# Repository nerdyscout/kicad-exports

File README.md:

**ℹ️ kicad-exports will not be updated anymore! As KiBot itself runs now in CI/CD, and there is this great [template](https://github.com/nerdyscout/KiBot-CICD-Template), even better automation can be done.**

---

Auto generate exports (schematics, gerbers, plots) for any KiCAD5 project.
You could run it locally or on every `git push` with Github Actions.

# usage of kicad-exports with Github Actions
```yaml
name: example

on:
  push:
    paths:
    - '**.sch'
    - '**.kicad_pcb'
  pull_request:
    paths:
      - '**.sch'
      - '**.kicad_pcb'

jobs:
  example:
    runs-on: ubuntu-latest
    steps:
    - uses: actions/checkout@v2
    - uses: nerdyscout/kicad-exports@v2.3.1
      with:
      # Required - kibot config file
        config: any.kibot.yaml
      # optional - prefix to output defined in config
        dir: docs
      # optional - schematic file
        schema: '*.sch'
      # optional - PCB design file
        board: '*.kicad_pcb'
      # optional - verbose output info
        verbose: 0
    - name: upload results
      uses: actions/upload-artifact@v2
      with:
        name: docs
        path: docs
```
The [predefined configs](/config) do run a ERC and DRC in advance, if these checks fail no exports will be generated. You could [write your own config](https://github.com/INTI-CMNB/kibot/tree/v0.8.0#the-configuration-file) file and define [filters](https://github.com/INTI-CMNB/kibot#filtering-drcerc-errors) to ignore these errors therefore forcing to export the data. In this case be careful not to end up with some faulty PCB.

> :warning: Pushing auto generated files back to the same branch you are working on manualy is a bad idea!

# use kicad-exports local 
## Installation
You need to have [Docker](https://www.docker.com/) installed.
```
git clone --recursive https://github.com/nerdyscout/kicad-exports /some/where/kicad-exports
cd /some/where/kicad-exports
make && make install
```

## run
go to your KiCad project folder and run kicad-exports
```
cd /my/kicad/example-project
kicad-exports -d $DIR_OUT -e $SCHEMA -b $BOARD -c $CONFIG 
```

> :warning: running any command your git repository will be modified using [kicad-git-filters](https://github.com/INTI-CMNB/kicad-git-filters/tree/v1.0.1)

### run with predefined example config
```
kicad-exports -c any.kibot.yaml 
```

### run with own config
place config file in directory of your kicad project and use relative path.
```
kicad-exports -c myconfig.kibot.yaml -v -s all
```
or run multiple config files
```
kicad-exports -c config/*.kibot.yaml -b myproject.kicad_pcb -e myproject.sch
```

### run bundle
[bundles](config/bundle) are a choice of configs run sequentially
```
kicad-exports -c config/bundle/documentation.default.kibot.lst
```

### generates a diff of the PCB between the given and the latest commit
```
kicad-exports -x $COMMIT_HASH -b myproject.kicad_pcb
```

## running localy enables additional paramaters
- `-v, --verbose` is useful while developing own config files
- `-o, --overwrite key=value` overwrite variables in config file
- `-s, --skip $arg` skips preflight from given config file 
- `-x, --diff $commit_hash` output differential files between $commit_hash and latest commit

# Credits
kicad-exports is just a wrapper for kibot and all it dependencies. For further details of all the tools used please see below.

- [KiBot](https://github.com/INTI-CMNB/kibot)
- [KiBoM](https://github.com/SchrodingersGat/KiBoM)
- [IBoM](https://github.com/openscopeproject/InteractiveHtmlBom/wiki/Usage)
- [kicad-automation-scripts](https://github.com/INTI-CMNB/kicad-automation-scripts)
- [PcbDraw](https://github.com/yaqwsx/PcbDraw)
- [kicad-git-filters](https://github.com/INTI-CMNB/kicad-git-filters)
- [KiCad-Diff](https://github.com/Gasman2014/KiCad-Diff)
- [kicad-boardview](https://github.com/whitequark/kicad-boardview)

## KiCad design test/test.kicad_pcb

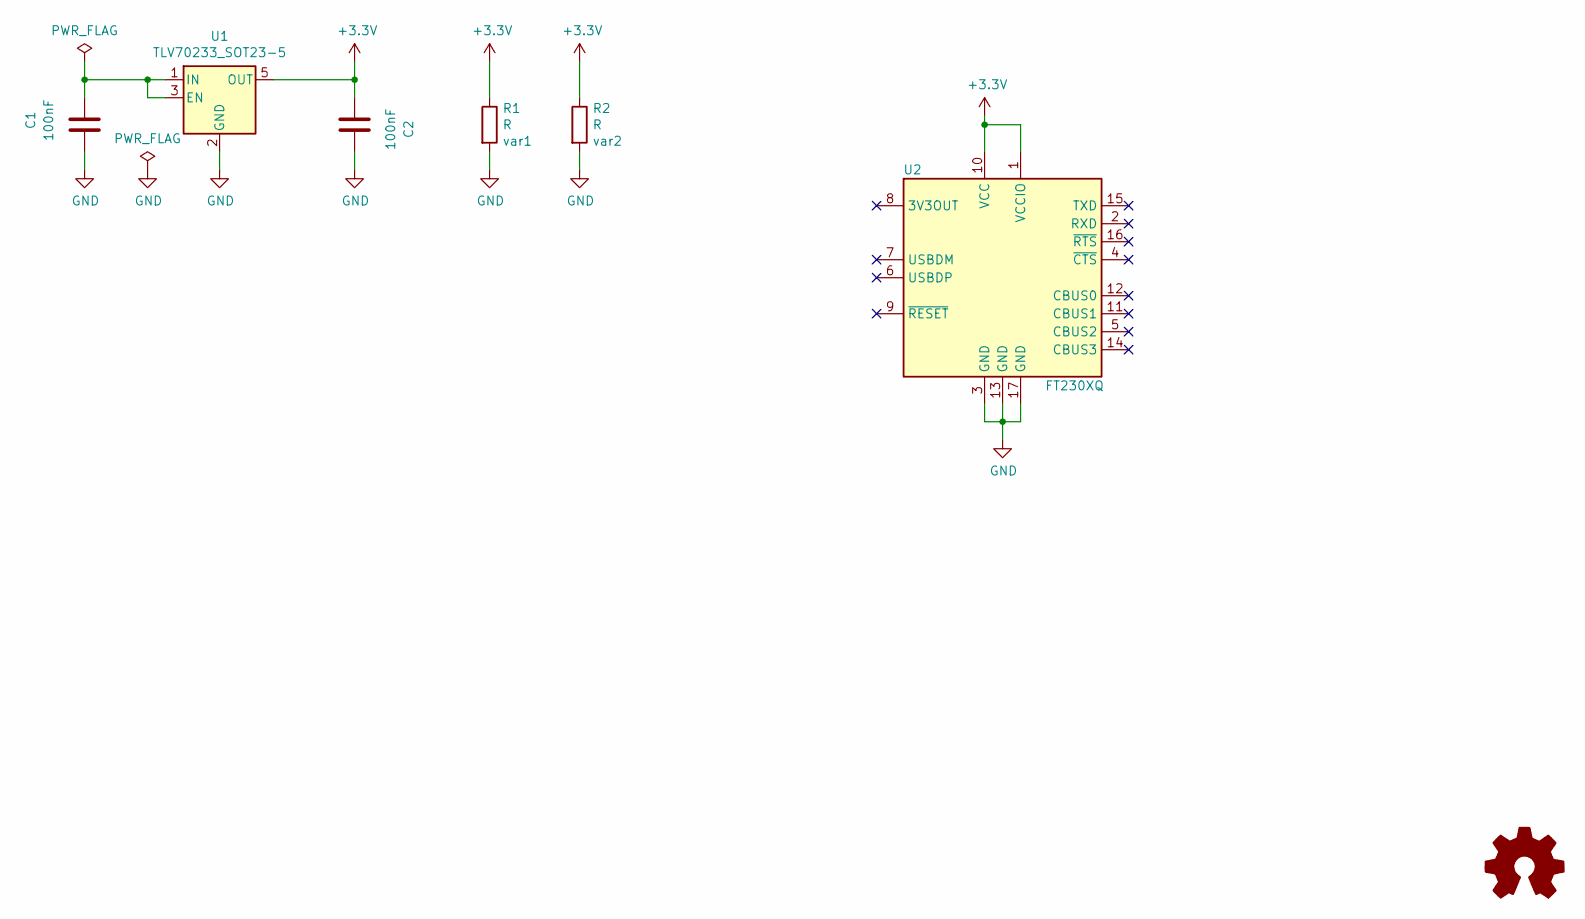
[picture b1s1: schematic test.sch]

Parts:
C1, C2: 100nF; C_1206_3216Metric; MPN CL10B104JB8NNND
LOGO1: Logo_Open_Hardware_Small; KiCad-Logo2_5mm_SilkScreen
R1: R; R_0805_2012Metric
R2: R; R_0805_2012Metric; MPN 1
U1: TLV70233_SOT23-5; SOT-23-5; MPN TLV70233PDBVT
U2: FT230XQ; QFN-16-1EP_4x4mm_P0.65mm_EP2.1x2.1mm; MPN FT230XQ-R

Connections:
+3V3: C2.2, R1.1, R2.1, U1.5 (OUT), U2.1 (VCCIO), U2.10 (VCC)
GND: C1.2, C2.1, R1.2, R2.2, U1.2 (GND), U2.3 (GND), U2.13 (GND), U2.17 (GND)
unnamed: C1.1, U1.1 (IN), U1.3 (EN)

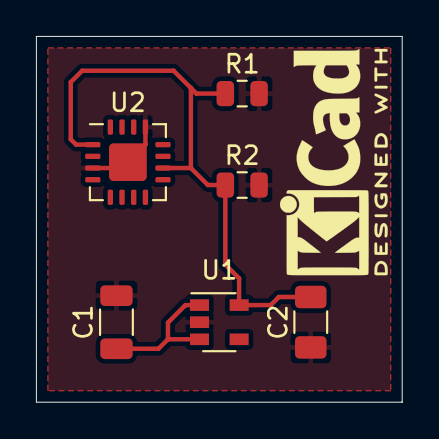
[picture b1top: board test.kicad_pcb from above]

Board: 2 copper layers, 20.3 x 20.3 mm, 7 parts (0 on the bottom side), 3 nets.

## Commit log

2020-05-24 init
2020-06-01 big update
2020-06-01 fixed some functions and improved docu
2020-06-06 Fixes issue #1
2020-06-06 init v0.3
2020-06-10 implemented main functionality
2020-06-10 pcbdraw is not used anyway
2020-06-10 fixes
2020-06-12 add tests
2020-06-12 fix url
2020-06-24 adding more components for testing
2020-06-24 add license
2020-06-24 removed PcbDraw
2020-06-24 added kicad-diff
2020-06-24 more compact install of kicad-automation-scripts
2020-06-24 improved script for upcomming v1.1
2020-07-03 better workflow including timestamps
2020-07-03 docu
2020-07-04 upper case all suffixes
2020-07-04 print board docu from pcbnew instead of kiplot
2020-07-04 stuff
2020-08-02 Refactor entrypoint script
2020-08-02 Use default bash to execute entrypoint
2020-08-02 Group messages; Fix arguments
2020-08-03 Fix illegal args
2020-08-03 fix: swap chmod and copy sequence
2020-08-03 Fix: schema parameter is -e, not -s
2020-08-03 Avoid passing empty parameters
2020-08-03 Fix: missing $ before EXIT_ERROR
2020-08-03 Fix: remove empty spaces in parameters process
2020-08-03 Fix empty space in default directory
2020-08-03 Fix: remove spaces in parameters
2020-08-03 moved mandatory parameters to optional
2020-08-03 calling kiplot works again
2020-08-03 improved docu
2020-08-04 Enable tests
2020-08-04 Fix syntax to pass arguments to docker
2020-08-04 Fix: more robust input processing
2020-08-04 made path conform
2020-08-05 Update issue templates
2020-08-06 add submodules
2020-08-06 debug
2020-08-06 recursive
2020-08-06 improved tests
2020-08-07 submodule
2020-08-08 fixup
2020-08-08 upgrade to v1.4.1
2020-08-08 fix moved styles of pcbdraw
2020-08-09 advanced config files
2020-08-11 bump submodule which have been lost on v2.0 merge
2020-08-19 fixed example
2020-09-28 fixed actions/upload-artifact version
2020-10-14 kibot
2020-10-16 removed tests
2020-10-16 modified templates
2020-10-16 improved docu and config
2020-10-18 fix user file permissions
2020-10-18 re-add kicad-git-filters
2020-10-23 v2.1b
2020-10-24 fixed documentation of changes pcbdraw path
2020-10-24 seperate tests
2020-10-24 add overwrite parameter
2020-11-04 Update README.md
    maybe im mistaken but i think the indentation in the readme example is wrong - atleast i needed to update it to get the workflow running ;)
2020-11-09 add discord server
2020-11-10 disable verbose
2020-11-12 more configs, runnig test, more putput
2020-11-12 octopart
2020-11-12 lcsc
2020-11-12 default
2020-11-12 oshpark
2020-11-12 jlcpcb
2020-11-13 add kicad-diff
2020-11-13 add more things to test exports
2020-11-14 update config files
2020-11-14 kicad-diff
2020-11-14 kicad-diff and run multi configs
2020-11-14 changed model config
2020-11-15 fix some kicad-diff related stuff
2020-11-15 enable overwrite in CI
2020-11-15 fix readme
2020-11-18 add display
2020-11-19 fix jlcpcb position kiplot config
2020-11-19 fix jlcpcb bom kiplot config
2020-11-20 fix filename testing
2020-11-20 rm old file
2020-11-20 add vendor to filenames
2020-12-01 rm discord server
2021-01-11 update packages
2021-01-12 changed test project
2021-01-30 introducing bundles
2021-02-13 moved kicad project used for test
2021-02-13 init new testing structure
2021-02-13 refactored all configs
2021-02-22 refactored tests
2021-02-22 auto set version for every build
2021-02-22 add gitignore
2021-03-02 can now run tests on config files
2021-03-02 'make update' updates docker images and submodules
2021-03-06 test are running
2021-03-07 fixed typo
2021-03-07 fixed the way the current path is mapped into docker
2021-03-07 tidy up build process
2021-03-07 improve tests
2021-04-04 test rework done
2021-04-04 add xml file
2021-04-04 further improvments of tests
2021-04-04 add generated data
2021-04-04 fix wrong links
2021-04-05 cleaned dockerhub repo and submodules
2021-04-05 kicad-export version correspond now to git tags
2021-04-05 rm kicad-diff
2021-04-05 re-add kicad-diff
2021-04-05 create custom hook for docker to init submodule
2021-04-08 clone repos directly instead of using it as a submodule
2021-04-08 optional parameters should be more optional now allowing kibot to choose schematic and board itself
2021-04-08 print current version on every run
2021-04-11 refactored how multiple configs are passed to kibot
2021-04-18 extra verbose level 1-4 can be used local + in CI
2021-04-18 bundle config needs extra handling in CI
2021-04-18 refactored bundels which use kibot.lst now
2021-04-18 return exit codes of kibot
2021-04-18 fix testing for filenames
2021-04-18 add extra info if board/schematic is not found
2021-04-18 fix color in comment of plot config
2021-04-19 change return value
2021-04-25 Revert "create custom hook for docker to init submodule"
    This reverts commit 2ce5b2765bdc7716e55004584aadb4539005db9b.
2021-04-25 pass testshellscript return value through makefile
2021-04-25 add boardview exporter
2021-04-25 fix issues noted by codefactor
2021-04-25 submodules are not used anymore
2021-04-25 add config to compress doc+fab output
2021-04-25 revert to latest
2021-04-25 fixes in boardview
2021-04-25 update autogenerated files
2021-04-25 codefactor.io
2021-04-29 Upgrade to GitHub-native Dependabot
2021-06-08 extension of config files does allow *.kibot.yaml as well as *.kibot.yml
2021-06-13 Create docs.kibot.yaml
    Fix file not found error
2021-06-13 Update README.md
    Correct indentation
2021-07-18 issue #29
2021-08-14 Update README.md
    update documentation
2021-10-24 added manufacterer suffix to bom files
2021-11-28 comment about archiving kicad-exports
